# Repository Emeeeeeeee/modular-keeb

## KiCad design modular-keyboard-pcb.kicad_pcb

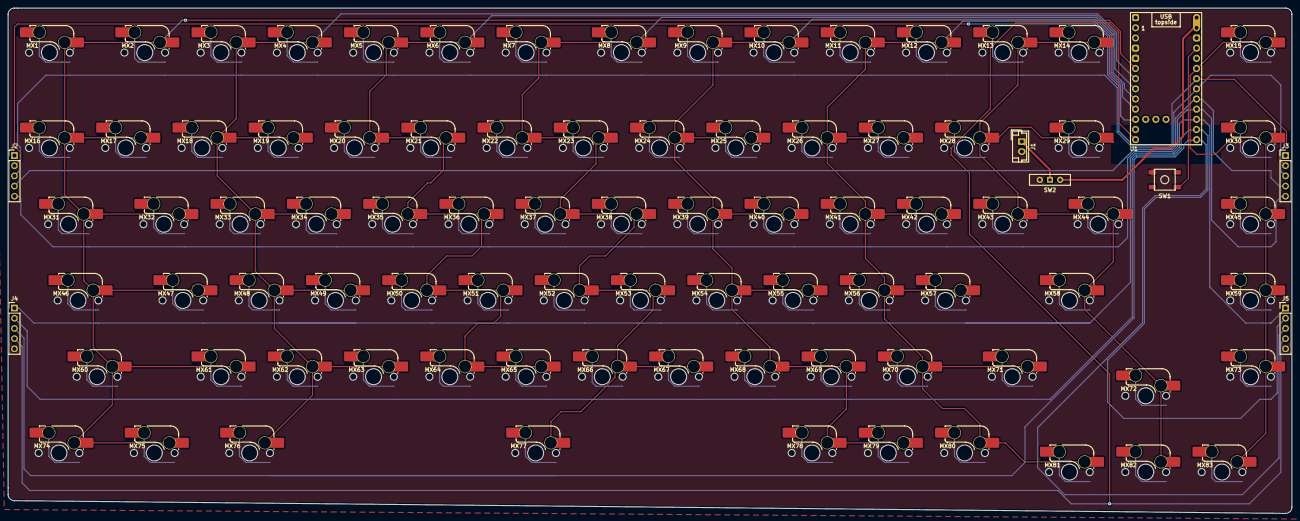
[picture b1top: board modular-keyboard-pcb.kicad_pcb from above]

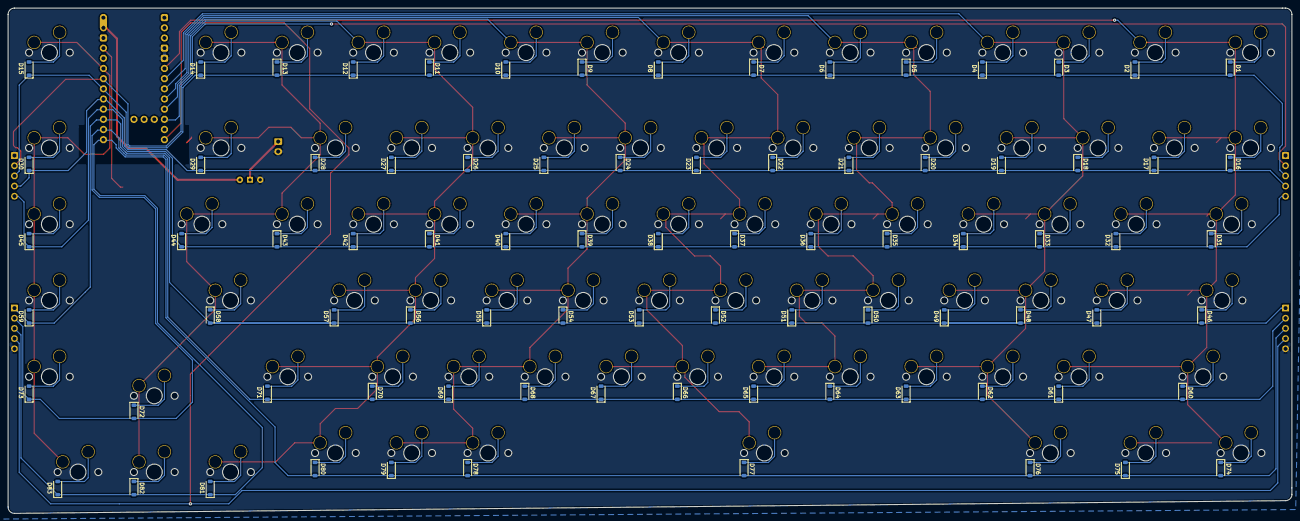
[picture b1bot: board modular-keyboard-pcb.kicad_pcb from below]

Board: 2 copper layers, 320.7 x 126.2 mm, 174 parts (83 on the bottom side), 103 nets.

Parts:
D1, D2, D3, D4, D5, D6, D7, D8, D9, D10, D11, D12, D13, D14, D15, D16, D17, D18, D19, D20, D21, D22, D23, D24, D25, D26, D27, D28, D29, D30, D31, D32, D33, D34, D35, D36, D37, D38, D39, D40, D41, D42, D43, D44, D45, D46, D47, D48, D49, D50, D51, D52, D53, D54, D55, D56, D57, D58, D59, D60, D61, D62, D63, D64, D65, D66, D67, D68, D69, D70, D71, D72, D73, D74, D75, D76, D77, D78, D79, D80, D81, D82, D83: D; D_SOD-123
J1: Conn_01x02; JST_EH_B2B-EH-A_1x02_P2.50mm_Vertical
J2, J3, J4, J5: mag_pogo_01x05; PinHeader_1x05_P2.54mm_Vertical
MX1, MX2, MX3, MX4, MX5, MX6, MX7, MX8, MX9, MX10, MX11, MX12, MX13, MX14, MX15, MX16, MX17, MX18, MX19, MX20, MX21, MX22, MX23, MX24, MX25, MX26, MX27, MX28, MX29, MX30, MX31, MX32, MX33, MX34, MX35, MX36, MX37, MX38, MX39, MX40, MX41, MX42, MX43, MX44, MX45, MX46, MX47, MX48, MX49, MX50, MX51, MX52, MX53, MX54, MX55, MX56, MX57, MX58, MX59, MX60, MX61, MX62, MX63, MX64, MX65, MX66, MX67, MX68, MX69, MX70, MX71, MX72, MX73, MX74, MX75, MX76, MX77, MX78, MX79, MX80, MX81, MX82, MX83: MX_SW_HS; SW_MX_HS_CPG151101S11_1u
SW1: SW_Push; SKQG-1155865
SW2: SW_Wuerth_450301014042; SW_Slide-03_Wuerth-WS-SLTV_10x2.5x6.4_P2.54mm
U1: nice_nano; nice_nano_AH_USBup

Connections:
Bat+: SW2.2 (C), U1.13 (BAT+)
Col 0: MX1.1, MX2.1, MX16.1, MX17.1, MX31.1, MX32.1, MX46.1, MX47.1, MX60.1, MX61.1, MX74.1, MX75.1, U1.5 (P0.17)
Col 1: MX3.1, MX4.1, MX18.1, MX19.1, MX33.1, MX34.1, MX48.1, MX49.1, MX62.1, MX63.1, MX76.1, U1.6 (P0.20)
Col 2: MX5.1, MX6.1, MX20.1, MX21.1, MX35.1, MX36.1, MX50.1, MX51.1, MX64.1, MX65.1, U1.7 (P0.22)
Col 3: MX7.1, MX8.1, MX22.1, MX23.1, MX37.1, MX38.1, MX52.1, MX53.1, MX66.1, MX67.1, MX77.1, U1.8 (P0.24)
Col 4: MX9.1, MX10.1, MX24.1, MX25.1, MX39.1, MX40.1, MX54.1, MX55.1, MX68.1, MX69.1, MX78.1, MX79.1, U1.9 (P1.00)
Col 5: MX11.1, MX12.1, MX26.1, MX27.1, MX41.1, MX42.1, MX56.1, MX57.1, MX70.1, MX71.1, MX80.1, MX81.1, U1.10 (P0.11)
Col 6: MX13.1, MX14.1, MX28.1, MX29.1, MX43.1, MX44.1, MX58.1, MX72.1, MX82.1, U1.11 (P1.04-LF)
Col 7: MX15.1, MX30.1, MX45.1, MX59.1, MX73.1, MX83.1, U1.17 (P0.31-LF)
Col 8: J2.2, J3.2, U1.18 (P0.29-LF)
Col 9: J4.4, J5.4, U1.12 (P1.06-LF)
GND: J1.2, J2.1, J3.1, J4.5, J5.5, SW1.2, SW2.3 (A), U1.3 (GND), U1.4 (GND), U1.14 (GND)
unnamed: D1.1 (K), MX1.2
unnamed: D2.2 (A), MX2.2
unnamed: D3.1 (K), MX3.2
unnamed: D4.2 (A), MX4.2
unnamed: D5.1 (K), MX5.2
unnamed: D6.2 (A), MX6.2
unnamed: D7.1 (K), MX7.2
unnamed: D8.2 (A), MX8.2
unnamed: D9.1 (K), MX9.2
unnamed: D10.2 (A), MX10.2
unnamed: D11.1 (K), MX11.2
unnamed: D12.2 (A), MX12.2
unnamed: D13.1 (K), MX13.2
unnamed: D14.2 (A), MX14.2
unnamed: D15.2 (A), MX15.2
unnamed: D16.1 (K), MX16.2
unnamed: D17.2 (A), MX17.2
unnamed: D18.1 (K), MX18.2
unnamed: D19.2 (A), MX19.2
unnamed: D20.1 (K), MX20.2
unnamed: D21.2 (A), MX21.2
unnamed: D22.1 (K), MX22.2
unnamed: D23.2 (A), MX23.2
unnamed: D24.1 (K), MX24.2
unnamed: D25.2 (A), MX25.2
unnamed: D26.1 (K), MX26.2
unnamed: D27.2 (A), MX27.2
unnamed: D28.1 (K), MX28.2
unnamed: D29.2 (A), MX29.2
unnamed: D30.2 (A), MX30.2
unnamed: D31.1 (K), MX31.2
unnamed: D32.2 (A), MX32.2
unnamed: D33.1 (K), MX33.2
unnamed: D34.2 (A), MX34.2
unnamed: D35.1 (K), MX35.2
unnamed: D36.2 (A), MX36.2
unnamed: D37.1 (K), MX37.2
unnamed: D38.2 (A), MX38.2
unnamed: D39.1 (K), MX39.2
unnamed: D40.2 (A), MX40.2
unnamed: D41.1 (K), MX41.2
unnamed: D42.2 (A), MX42.2
unnamed: D43.1 (K), MX43.2
unnamed: D44.2 (A), MX44.2
unnamed: D45.2 (A), MX45.2
unnamed: D46.1 (K), MX46.2
unnamed: D47.2 (A), MX47.2
unnamed: D48.1 (K), MX48.2
unnamed: D49.2 (A), MX49.2
unnamed: D50.1 (K), MX50.2
unnamed: D51.2 (A), MX51.2
unnamed: D52.1 (K), MX52.2
unnamed: D53.2 (A), MX53.2
unnamed: D54.1 (K), MX54.2
unnamed: D55.2 (A), MX55.2
unnamed: D56.1 (K), MX56.2
unnamed: D57.2 (A), MX57.2
unnamed: D58.1 (K), MX58.2
unnamed: D59.2 (A), MX59.2
unnamed: D60.1 (K), MX60.2
unnamed: D61.2 (A), MX61.2
unnamed: D62.1 (K), MX62.2
unnamed: D63.2 (A), MX63.2
unnamed: D64.1 (K), MX64.2
unnamed: D65.2 (A), MX65.2
unnamed: D66.1 (K), MX66.2
unnamed: D67.2 (A), MX67.2
unnamed: D68.1 (K), MX68.2
unnamed: D69.2 (A), MX69.2
unnamed: D70.1 (K), MX70.2
unnamed: D71.2 (A), MX71.2
unnamed: D72.1 (K), MX72.2
unnamed: D73.2 (A), MX73.2
unnamed: D74.1 (K), MX74.2
unnamed: D75.2 (A), MX75.2
unnamed: D76.1 (K), MX76.2
unnamed: D77.1 (K), MX77.2
unnamed: D78.1 (K), MX78.2
unnamed: D79.2 (A), MX79.2
unnamed: D80.1 (K), MX80.2
unnamed: D81.2 (A), MX81.2
unnamed: D82.1 (K), MX82.2
unnamed: D83.2 (A), MX83.2
unnamed: J1.1, SW2.1 (B)
unnamed: SW1.1, U1.15 (RST)
Row 0: D1.2 (A), D2.1 (K), D3.2 (A), D4.1 (K), D5.2 (A), D6.1 (K), D7.2 (A), D8.1 (K), D9.2 (A), D10.1 (K), D11.2 (A), D12.1 (K), D13.2 (A), D14.1 (K), D15.1 (K), J2.3, J3.3, U1.19 (P0.02-LF)
Row 1: D16.2 (A), D17.1 (K), D18.2 (A), D19.1 (K), D20.2 (A), D21.1 (K), D22.2 (A), D23.1 (K), D24.2 (A), D25.1 (K), D26.2 (A), D27.1 (K), D28.2 (A), D29.1 (K), D30.1 (K), J2.4, J3.4, U1.20 (P1.15-LF)
Row 2: D31.2 (A), D32.1 (K), D33.2 (A), D34.1 (K), D35.2 (A), D36.1 (K), D37.2 (A), D38.1 (K), D39.2 (A), D40.1 (K), D41.2 (A), D42.1 (K), D43.2 (A), D44.1 (K), D45.1 (K), J2.5, J3.5, U1.21 (P1.13-LF)
Row 3: D46.2 (A), D47.1 (K), D48.2 (A), D49.1 (K), D50.2 (A), D51.1 (K), D52.2 (A), D53.1 (K), D54.2 (A), D55.1 (K), D56.2 (A), D57.1 (K), D58.2 (A), D59.1 (K), J4.1, J5.1, U1.22 (P1.11-LF)
Row 4: D60.2 (A), D61.1 (K), D62.2 (A), D63.1 (K), D64.2 (A), D65.1 (K), D66.2 (A), D67.1 (K), D68.2 (A), D69.1 (K), D70.2 (A), D71.1 (K), D72.2 (A), D73.1 (K), J4.2, J5.2, U1.23 (P0.10-LF)
Row 5: D74.2 (A), D75.1 (K), D76.2 (A), D77.2 (A), D78.2 (A), D79.1 (K), D80.2 (A), D81.1 (K), D82.2 (A), D83.1 (K), J4.3, J5.3, U1.24 (P0.09-LF)

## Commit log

2026-05-25 startup
2026-05-25 Add submodules
2026-05-25 edit 1
2026-05-26 libaries added
2026-05-26 day 1
2026-05-27 day 2
    changed to nice nano
2026-05-27 day 2 end
2026-05-27 day 3 edit 1
    schematic finalized
2026-05-28 day 3
2026-05-29 pcb mostly done
2026-05-29 PCB done?
2026-05-29 final pcb?
2026-05-29 pcb final tweak before review
